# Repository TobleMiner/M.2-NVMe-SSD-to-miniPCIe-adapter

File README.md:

M.2 Key M to miniPCIe adapter
=============================

Especially slightly aged PCIe-enabled equipment intended for computer
networking applications often feature miniPCIe slots. Adding storage
capability to this type of device can be difficult. Even if one or more
of the mini PCIe slots are SATA-enabled availability of fitting mSATA SSDs
is continually becoming worse as mSATA SSDs have started to drift into
obscurity.  
This project is aimed at providing an option for fast, high reliability
NVMe-based storage in devices that do not have any M.2 Key M but only
miniPCIe slots.  
One example of such a device is the PCengines APU2, an AMD64 network
platform with up to two PCIe-enabled miniPCIe slots.

## Compatible SSDs

A bit of care has to be taken when selecting a SSD compatible with the
adapter. It only supports 2230 and 2242 M.2 PCIe SSDs. The more common
2280 size is not supported due to size constraints.  
Depending on the device the adapter is to be used in even 2242 M.2 SSDs
might not fit.  
I've had good sucess using Samsung PM991 NVMe SSDs.

# Ordering

The fabrication files inside `fab` are JLCPCB-ready. The board must be
ordered with a 1.0mm board thickness to fit the miniPCIe slot.  
Additionally I'd highly recommend selecting the "controlled impedance"
option with 7628 stackup. The PCIe interface has been routed with that
stackup in mind.

## Limitations

Currently this board does neither use gold plating nor edge beveling on
the miniPCIe contact fingers. While good for cost reduction in small
production runs this is not ideal.  
When ordering through JLCPCB at the time of writing the PCB would have
to be adjusted (minimum size 70x70mm) to be able to get beveled edges
and gold plating.

# Use

The following picture shows two of the adapters installed in an APU2
with Samsung PM991 NVMe SSDs.

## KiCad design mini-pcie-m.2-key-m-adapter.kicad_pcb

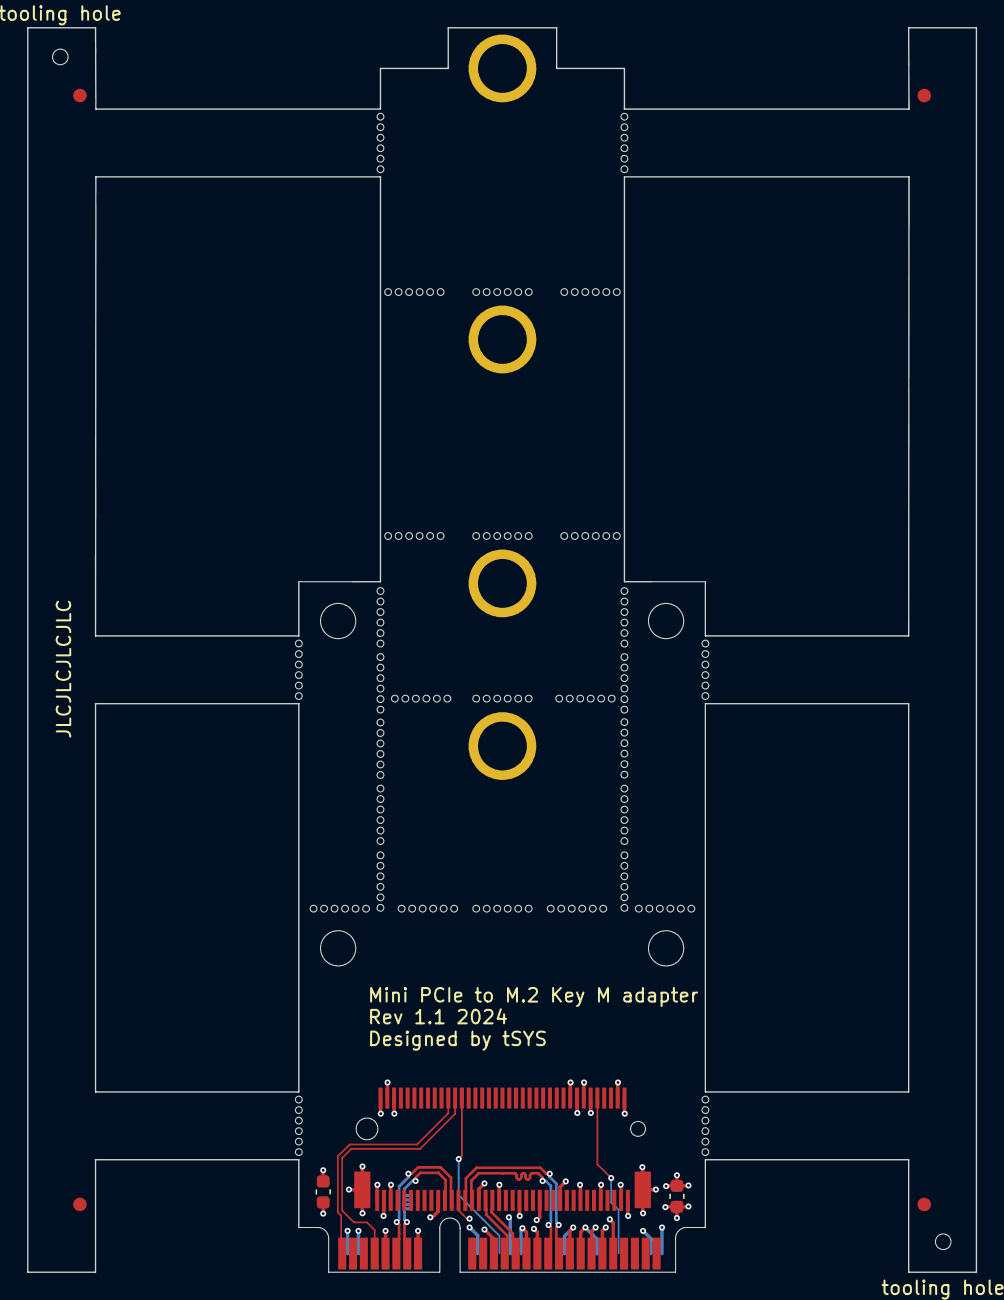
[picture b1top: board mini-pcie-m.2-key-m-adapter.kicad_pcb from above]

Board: 4 copper layers, 70.0 x 91.8 mm, 6 parts (0 on the bottom side), 12 nets.

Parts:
C1, C2: 22uF; C_0603_1608Metric
H2, H3: MountingHole; ToolingHole_JLCSMT
J1: miniPCIe; mini-PCIe_F1_Full
J2: Bus_M.2_Socket_M; MDTXXXXXX001

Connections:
+3V3: C1.1, C2.1, J1.2 (+3.3Vaux), J1.24 (+3.3Vaux), J1.39 (+3.3Vaux), J1.41 (+3.3Vaux), J1.52 (+3.3Vaux), J2.2 (3.3V), J2.4 (3.3V), J2.12 (3.3V), J2.14 (3.3V), J2.16 (3.3V), J2.18 (3.3V), J2.70 (3.3V), J2.72 (3.3V), J2.74 (3.3V)
/CLK+: J1.13 (REF_CLK+), J2.55 (REFCLKp)
/CLK-: J1.11 (REF_CLK-), J2.53 (REFCLKn)
/RX+: J1.25 (PERp0), J2.41 (PERn0/SATA-B+)
/RX-: J1.23 (PERn0), J2.43 (PERp0/SATA-B-)
/TX+: J1.33 (PETp0), J2.49 (PETp0/SATA-A+)
/TX-: J1.31 (PETn0), J2.47 (PETn0/SATA-A-)
/~LED: J1.44 (~LED_WLAN), J2.10 (DAS/~DSS/~LED1)
/~REQ: J1.7 (~CLKREQ), J2.52 (~CLKREQ)
/~RST: J1.22 (~PERST), J2.50 (~PERST)
/~WAKE: J1.1 (~WAKE), J2.54 (~PEWAKE)
GND: C1.2, C2.2, J1.4 (GND), J1.9 (GND), J1.15 (GND), J1.18 (GND), J1.21 (GND), J1.26 (GND), J1.27 (GND), J1.29 (GND), J1.34 (GND), J1.35 (GND), J1.37 (GND), J1.40 (GND), J1.43 (GND), J1.50 (GND), J2.1 (GND), J2.3 (GND), J2.9 (GND), J2.15 (GND), J2.21 (GND), J2.27 (GND), J2.33 (GND), J2.39 (GND), J2.45 (GND), J2.51 (GND), J2.57 (GND), J2.71 (GND), J2.73 (GND), J2.75 (GND), J2.MP

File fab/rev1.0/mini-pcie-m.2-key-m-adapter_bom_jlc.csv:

"Comment","Designator","Footprint","LCSC Part #"
"22uF","C1,C2","C_0603_1608Metric","C59461"
"MountingHole_Pad","H1","MountingHole_3.6mm_small","C2928188"
"Bus_M.2_Socket_M","J2","MDTXXXXXX001","C2832351"

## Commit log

2022-11-19 Add README
2022-11-19 Add M.2 connector 3D model
2022-11-19 Add adapter photos
2022-11-19 Remove /fab and JLC fabrication files from gitignore
2022-11-19 Add fabrication files
2022-11-19 Add schematic pdf export
2022-11-19 Add note on limitations regarding beveled edges and gold plating
2023-02-13 Update README.md
    Changed board thickness on line 30 from 1.2mm to 1.0mm - I ordered a batch with 1.2mm and found they do not fit, and a quick Google search indicates the miniPCIe spec is 1.0mm.
2024-03-18 lib: ToolingHole: update to latest version
    New version has fiducials and mousebites for JLC standard assembly
2024-03-18 lib: kicad-mini-pci-e: add half-size mounting holes to mini PCIe card
2024-03-18 Add 60mm and 90mm M.2 mounting options
2024-03-18 Add 60mm and 80mm M.2 mounting options
